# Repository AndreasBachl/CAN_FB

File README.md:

# CAN_FB_Hardware
PCB layouts for CAN field bus devices.

The layouts are stored in AUTODESK Eagle format.

Be aware that CAN does not contain any security measures.

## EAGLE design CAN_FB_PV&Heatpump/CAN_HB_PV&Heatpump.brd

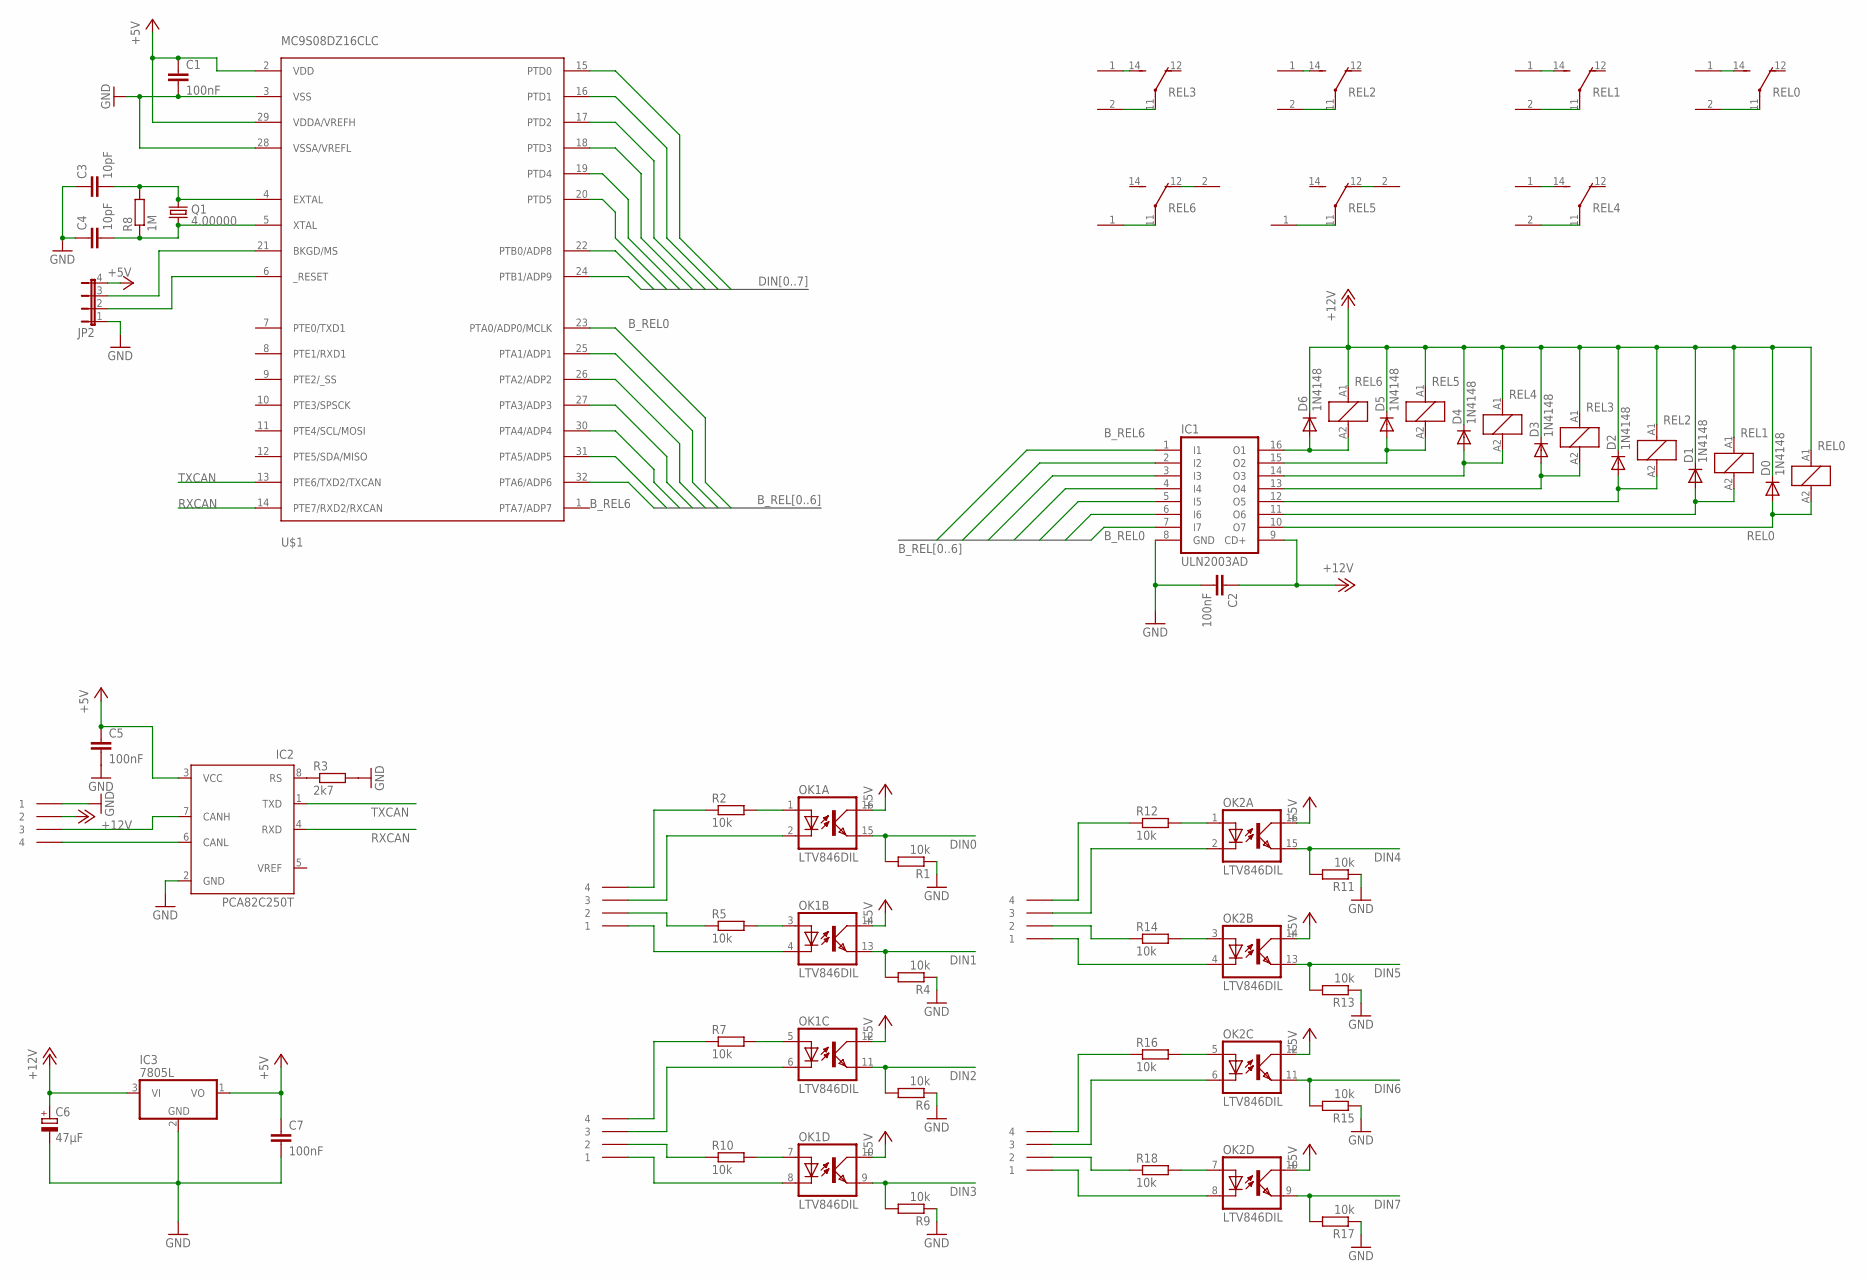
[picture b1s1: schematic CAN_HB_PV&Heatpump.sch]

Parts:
C1, C7: 100nF; C0805K
C2, C5: 100nF; C0805
C3, C4: 10pF; C0805K
C6: 47µF; E2-5
D0, D1, D2, D3, D4, D5, D6: 1N4148; SOD80C
IC1: ULN2003AD; SO16
IC2: PCA82C250T; SO8
IC3: 7805L; TO92
JP2: JP4E; JP4
KL1, KL2, KL3, KL4, KL5: AST021-04
OK1, OK2: LTV846DIL; DIL16
Q1: 4.00000; HC49U-V
R1, R2, R4, R5, R6, R7, R9, R10, R11, R12, R13, R14, R15, R16, R17, R18: 10k; R0805
R3: 2k7; R0805
R8: 1M; R0805
REL0, REL1, REL2, REL3, REL4, REL5, REL6: FIN34.51FIN34.51.7; FIN34
U$1: MC9S08DZ16CLC; LQFP32
U$2, U$3, U$4, U$5, U$6, U$14, U$15: AKL320-02

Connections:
+5V: C1.1, C5.1, C7.1, IC2.3 (VCC), IC3.1 (VO), JP2.4, OK1.10 (COL), OK1.12 (COL), OK1.14 (COL), OK1.16 (COL), OK2.10 (COL), OK2.12 (COL), OK2.14 (COL), OK2.16 (COL), U$1.2 (VDD), U$1.29 (VDDA/VREFH)
+12V: C2.1, C6.+, D0.C, D1.C, D2.C, D3.C, D4.C, D5.C, D6.C, IC1.9 (CD+), IC3.3 (VI), KL1.P$2 (2), REL0.A1 (1), REL1.A1 (1), REL2.A1 (1), REL3.A1 (1), REL4.A1 (1), REL5.A1 (1), REL6.A1 (1)
BKGD: JP2.3, U$1.21 (BKGD/MS)
B_REL0: IC1.7 (I7), U$1.23 (PTA0/ADP0/MCLK)
B_REL1: IC1.6 (I6), U$1.25 (PTA1/ADP1)
B_REL2: IC1.5 (I5), U$1.26 (PTA2/ADP2)
B_REL3: IC1.4 (I4), U$1.27 (PTA3/ADP3)
B_REL4: IC1.3 (I3), U$1.30 (PTA4/ADP4)
B_REL5: IC1.2 (I2), U$1.31 (PTA5/ADP5)
B_REL6: IC1.1 (I1), U$1.32 (PTA6/ADP6)
CANH: IC2.7 (CANH), KL1.P$3 (3)
CANL: IC2.6 (CANL), KL1.P$4 (4)
CH4: REL5.12 (O), U$5.2
DIN0: OK1.15 (EMIT), R1.2, U$1.15 (PTD0)
DIN0+: KL2.P$4 (4), R2.1
DIN0-: KL2.P$3 (3), OK1.2 (C)
DIN1: OK1.13 (EMIT), R4.2, U$1.16 (PTD1)
DIN1+: KL2.P$2 (2), R5.1
DIN1-: KL2.P$1 (1), OK1.4 (C)
DIN2: OK1.11 (EMIT), R6.2, U$1.17 (PTD2)
DIN2+: KL3.P$4 (4), R7.1
DIN2-: KL3.P$3 (3), OK1.6 (C)
DIN3: OK1.9 (EMIT), R9.2, U$1.18 (PTD3)
DIN3+: KL3.P$2 (2), R10.1
DIN3-: KL3.P$1 (1), OK1.8 (C)
DIN4: OK2.15 (EMIT), R11.2, U$1.19 (PTD4)
DIN4+: KL4.P$4 (4), R12.1
DIN4-: KL4.P$3 (3), OK2.2 (C)
DIN5: OK2.13 (EMIT), R13.2, U$1.20 (PTD5)
DIN5+: KL4.P$2 (2), R14.1
DIN5-: KL4.P$1 (1), OK2.4 (C)
DIN6: OK2.11 (EMIT), R15.2, U$1.22 (PTB0/ADP8)
DIN6+: KL5.P$4 (4), R16.1
DIN6-: KL5.P$3 (3), OK2.6 (C)
DIN7: OK2.9 (EMIT), R17.2, U$1.24 (PTB1/ADP9)
DIN7+: KL5.P$2 (2), R18.1
DIN7-: KL5.P$1 (1), OK2.8 (C)
GND: C1.2, C2.2, C3.1, C4.1, C5.2, C6.-, C7.2, IC1.8 (GND), IC2.2 (GND), IC3.2 (GND), JP2.1, KL1.P$1 (1), R1.1, R3.2, R4.1, R6.1, R9.1, R11.1, R13.1, R15.1, R17.1, U$1.3 (VSS), U$1.28 (VSSA/VREFL)
unnamed: REL3.11, U$2.2
unnamed: OK1.1 (A), R2.2
unnamed: IC2.8 (RS), R3.1
unnamed: REL6.11, U$3.1
unnamed: REL3.14 (S), U$2.1
unnamed: REL2.14 (S), U$4.1
unnamed: REL2.11, U$4.2
unnamed: C4.2, Q1.1, R8.1, U$1.5 (XTAL)
unnamed: C3.2, Q1.2, R8.2, U$1.4 (EXTAL)
unnamed: REL4.11, U$14.2
unnamed: REL4.14 (S), U$14.1
unnamed: REL1.11, U$6.2
unnamed: REL1.14 (S), U$6.1
unnamed: REL0.11, U$15.2
unnamed: REL0.14 (S), U$15.1
unnamed: REL5.11, U$5.1
unnamed: REL6.12 (O), U$3.2
unnamed: OK1.3 (A), R5.2
unnamed: OK1.5 (A), R7.2
unnamed: OK1.7 (A), R10.2
unnamed: OK2.1 (A), R12.2
unnamed: OK2.3 (A), R14.2
unnamed: OK2.5 (A), R16.2
unnamed: OK2.7 (A), R18.2
REL0: D0.A, IC1.10 (O7), REL0.A2 (2)
REL1: D1.A, IC1.11 (O6), REL1.A2 (2)
REL2: D2.A, IC1.12 (O5), REL2.A2 (2)
REL3: D3.A, IC1.13 (O4), REL3.A2 (2)
REL4: D4.A, IC1.14 (O3), REL4.A2 (2)
REL5: D5.A, IC1.15 (O2), REL5.A2 (2)
REL6: D6.A, IC1.16 (O1), REL6.A2 (2)
RESET: JP2.2, U$1.6 (_RESET)
RXCAN: IC2.4 (RXD), U$1.14 (PTE7/RXD2/RXCAN)
TXCAN: IC2.1 (TXD), U$1.13 (PTE6/TXD2/TXCAN)

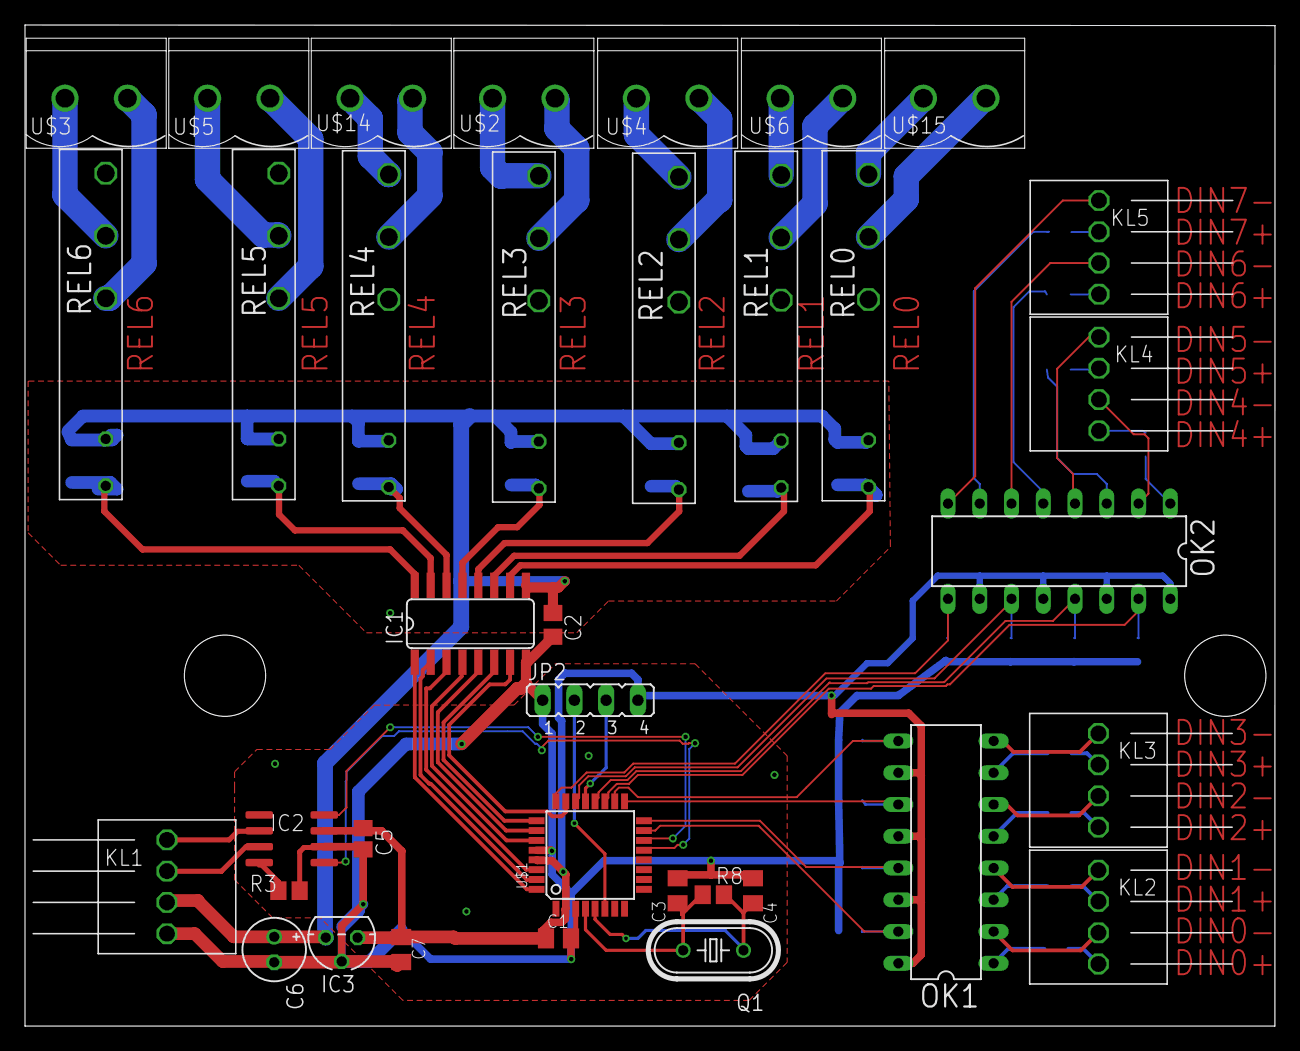
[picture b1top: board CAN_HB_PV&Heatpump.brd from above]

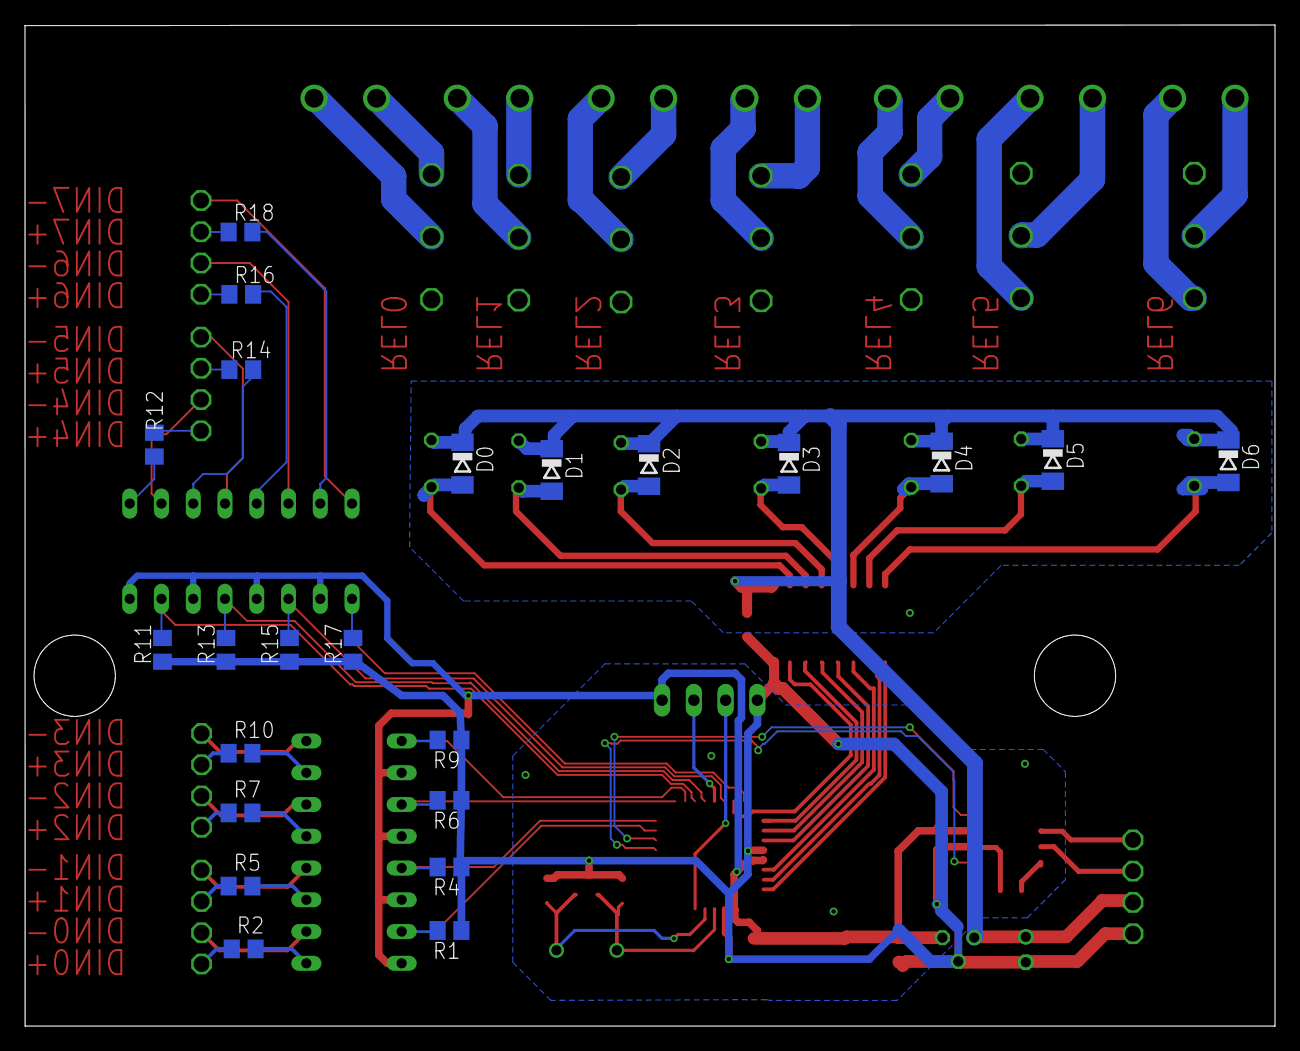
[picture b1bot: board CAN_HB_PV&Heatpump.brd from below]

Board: 2 copper layers, 100.0 x 80.1 mm, 59 parts (23 on the bottom side), 72 nets.

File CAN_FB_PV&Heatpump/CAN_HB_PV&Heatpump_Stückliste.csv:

"Qty";"Value";"Device";"Package";"Parts";"Description";"";
"1";"";"JP4E";"JP4";"JP2";"JUMPER";"";
"6";"";"R-EU_R0805";"R0805";"R7, R10, R12, R14, R16, R18";"RESISTOR, European symbol";"";
"2";"100nF";"C-EUC0805";"C0805";"C2, C5";"CAPACITOR, European symbol";"";
"2";"100nF";"C-EUC0805K";"C0805K";"C1, C7";"CAPACITOR, European symbol";"";
"10";"10k";"R-EU_R0805";"R0805";"R1, R2, R4, R5, R6, R9, R11, R13, R15, R17";"RESISTOR, European symbol";"";
"2";"10pF";"C-EUC0805K";"C0805K";"C3, C4";"CAPACITOR, European symbol";"";
"1";"1M";"R-EU_R0805";"R0805";"R8";"RESISTOR, European symbol";"";
"7";"1N4148";"DIODE-SOD80C";"SOD80C";"D0, D1, D2, D3, D4, D5, D6";"DIODE";"";
"1";"2k7";"R-EU_R0805";"R0805";"R3";"RESISTOR, European symbol";"";
"1";"4.00000";"CRYTALHC49U-V";"HC49U-V";"Q1";"CRYSTAL";"";
"1";"47µF";"CPOL-EUE2-5";"E2-5";"C6";"POLARIZED CAPACITOR, European symbol";"";
"1";"7805L";"7805L";"TO92";"IC3";"Positive VOLTAGE REGULATOR";"";
"7";"AKL320-02";"AKL320-02";"AKL320-02";"U$2, U$3, U$4, U$5, U$6, U$14, U$15";"";"";
"5";"AST021-04";"AST021-04";"AST021-04";"KL1, KL2, KL3, KL4, KL5";"";"";
"7";"FIN34.51FIN34.51.7";"FIN34.51FIN34.51.7";"FIN34";"REL0, REL1, REL2, REL3, REL4, REL5, REL6";"Finder 34.51.7 Relais";"";
"2";"LTV846DIL";"LTV846DIL";"DIL16";"OK1, OK2";"OPTO COUPLER";"";
"1";"MC9S08DZ16CLC";"MC9S08DZ16CLC";"LQFP32";"U$1";"";"";
"1";"PCA82C250T";"PCA82C250T";"SO8";"IC2";"CAN CONTROLLER INTERFACE";"";
"1";"ULN2003AD";"ULN2003AD";"SO16";"IC1";"DRIVER ARRAY";"";

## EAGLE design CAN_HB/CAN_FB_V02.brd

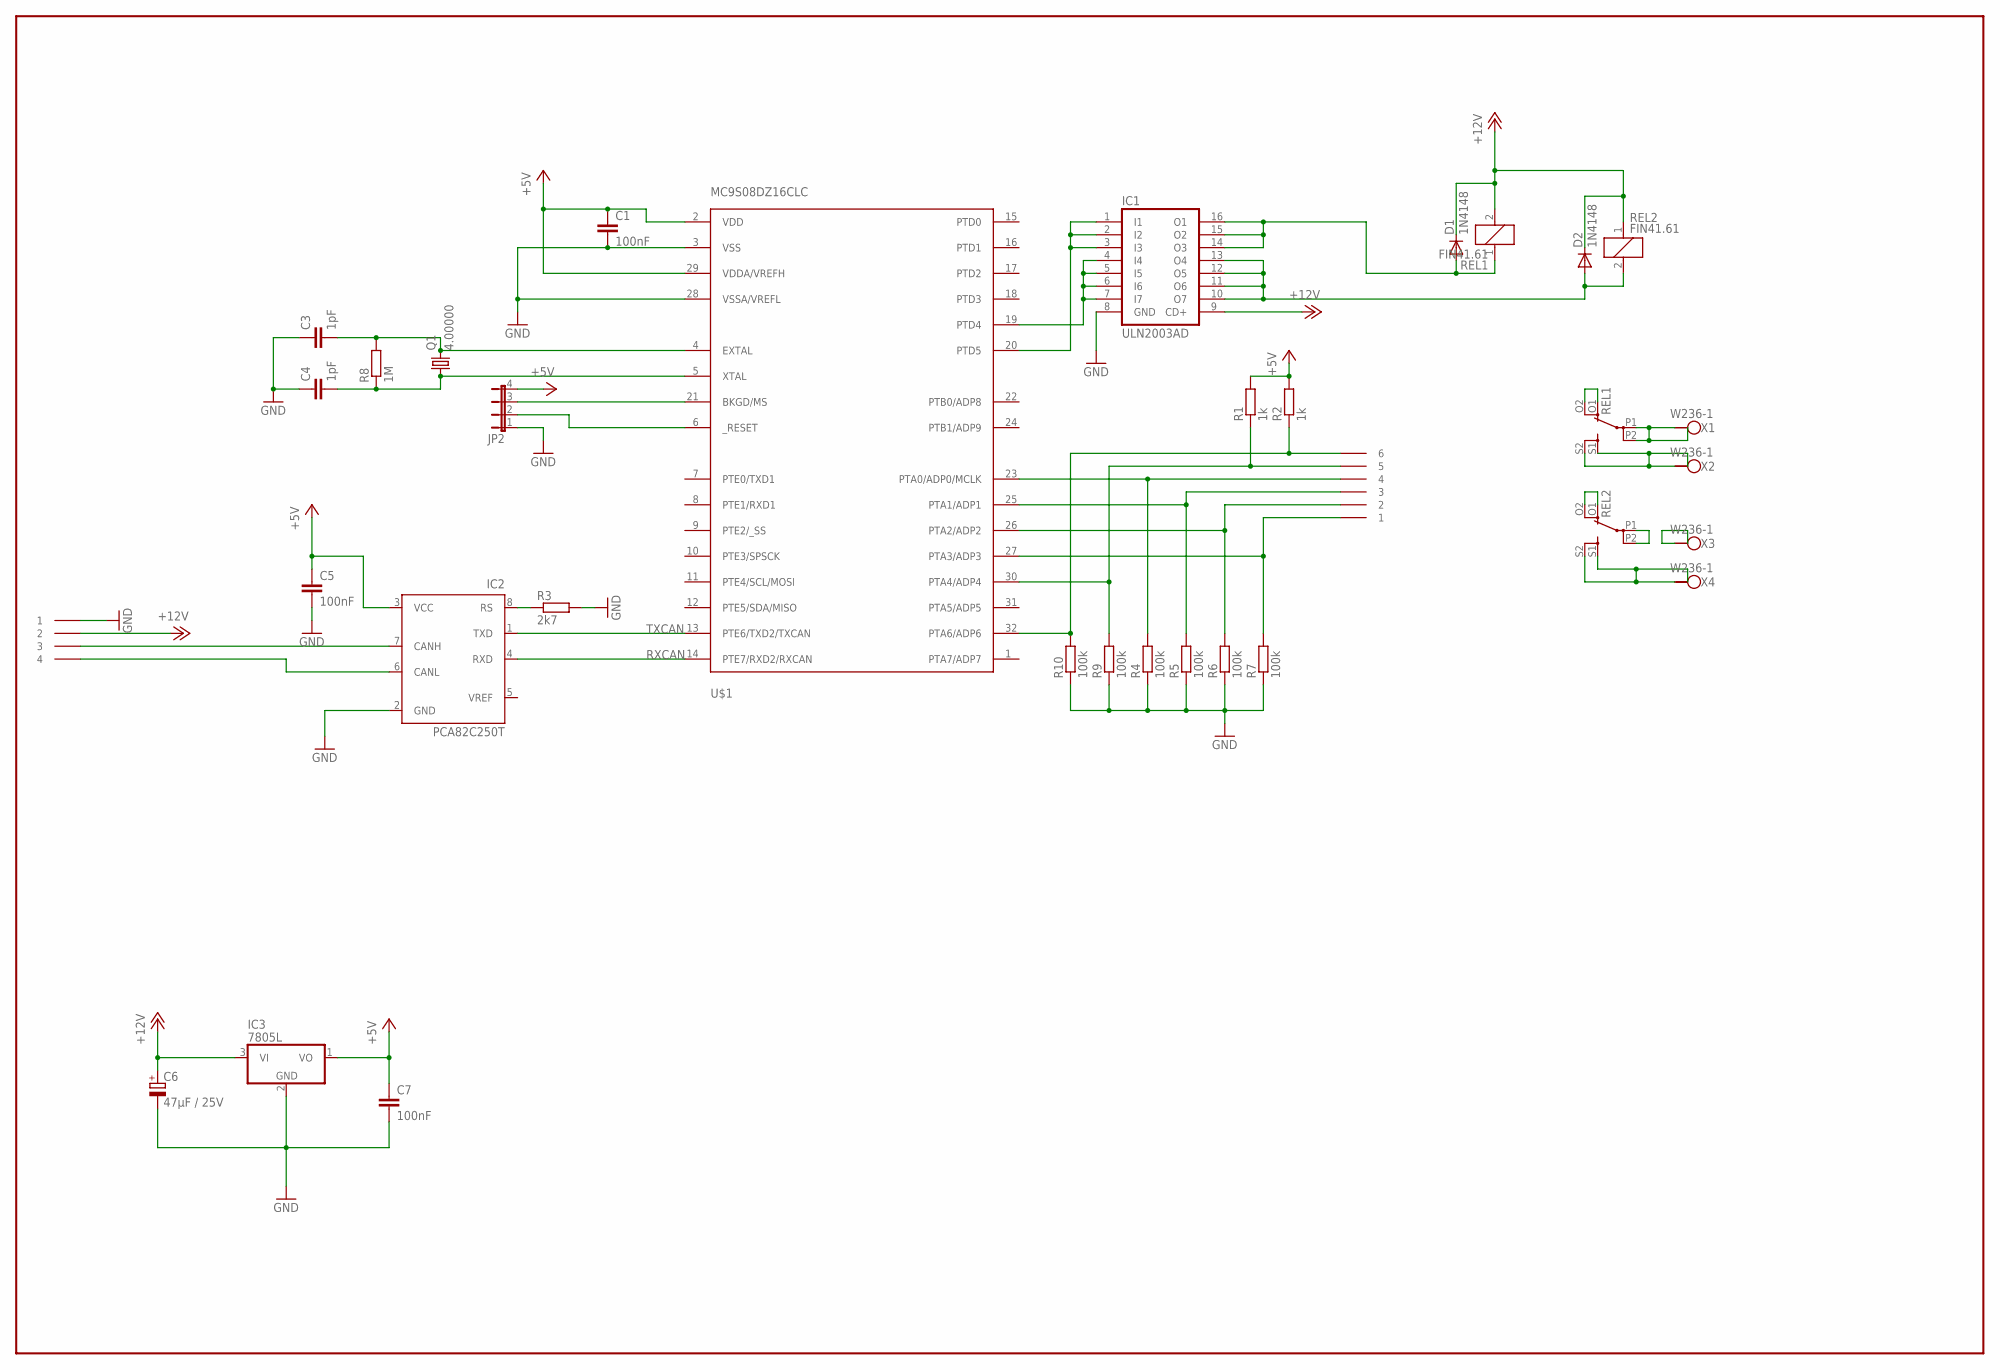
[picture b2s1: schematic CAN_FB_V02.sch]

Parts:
C1, C7: 100nF; C0805K
C3, C4: 1pF; C0805K
C5: 100nF; C0805
C6: 47µF / 25V; E2-5
D1, D2: 1N4148; SOD80C
IC1: ULN2003AD; SO16
IC2: PCA82C250T; SO8
IC3: 7805L; TO92
JP2: JP4E; JP4
KL1: AST021-04
KL2: AST021-06
Q1: 4.00000; HC49U-V
R1, R2: 1k; R0805
R3: 2k7; R0805
R4, R5, R6, R7, R9, R10: 100k; R0805
R8: 1M; R0805
REL1, REL2: FIN41.61; FIN41
U$1: MC9S08DZ16CLC; LQFP32
X1, X2, X3, X4: W236-1

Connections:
+5V: C1.1, C5.1, C7.1, IC2.3 (VCC), IC3.1 (VO), JP2.4, R1.2, R2.2, U$1.2 (VDD), U$1.29 (VDDA/VREFH)
+12V: C6.+, D1.C, D2.C, IC1.9 (CD+), IC3.3 (VI), KL1.P$2 (2), REL1.2, REL2.1
A0: KL2.P$4 (4), R4.2, U$1.23 (PTA0/ADP0/MCLK)
A1: KL2.P$3 (3), R5.2, U$1.25 (PTA1/ADP1)
A2: KL2.P$2 (2), R6.2, U$1.26 (PTA2/ADP2)
A3: KL2.P$1 (1), R7.2, U$1.27 (PTA3/ADP3)
A4: KL2.P$5 (5), R1.1, R9.2, U$1.30 (PTA4/ADP4)
A5: KL2.P$6 (6), R2.1, R10.2, U$1.32 (PTA6/ADP6)
GND: C1.2, C3.1, C4.1, C5.2, C6.-, C7.2, IC1.8 (GND), IC2.2 (GND), IC3.2 (GND), JP2.1, KL1.P$1 (1), R3.2, R4.1, R5.1, R6.1, R7.1, R9.1, R10.1, U$1.3 (VSS), U$1.28 (VSSA/VREFL)
unnamed: IC2.8 (RS), R3.1
unnamed: IC2.6 (CANL), KL1.P$4 (4)
unnamed: D1.A, IC1.14 (O3), IC1.15 (O2), IC1.16 (O1), REL1.1
unnamed: IC2.7 (CANH), KL1.P$3 (3)
unnamed: D2.A, IC1.10 (O7), IC1.11 (O6), IC1.12 (O5), IC1.13 (O4), REL2.2
unnamed: C4.2, Q1.1, R8.1, U$1.5 (XTAL)
unnamed: C3.2, Q1.2, R8.2, U$1.4 (EXTAL)
unnamed: IC1.1 (I1), IC1.2 (I2), IC1.3 (I3), U$1.20 (PTD5)
unnamed: IC1.4 (I4), IC1.5 (I5), IC1.6 (I6), IC1.7 (I7), U$1.19 (PTD4)
unnamed: REL1.S1 (S), REL1.S2 (S), X2.1 (KL1), X2.2 (KL2)
unnamed: REL1.P1, REL1.P2, X1.1 (KL1), X1.2 (KL2)
unnamed: REL1.O1 (O), REL1.O2 (O)
unnamed: JP2.2, U$1.6 (_RESET)
unnamed: JP2.3, U$1.21 (BKGD/MS)
unnamed: REL2.O1 (O), REL2.O2 (O)
unnamed: X3.1 (KL1), X3.2 (KL2)
unnamed: REL2.S1 (S), REL2.S2 (S), X4.1 (KL1), X4.2 (KL2)
unnamed: REL2.P1, REL2.P2
RXCAN: IC2.4 (RXD), U$1.14 (PTE7/RXD2/RXCAN)
TXCAN: IC2.1 (TXD), U$1.13 (PTE6/TXD2/TXCAN)

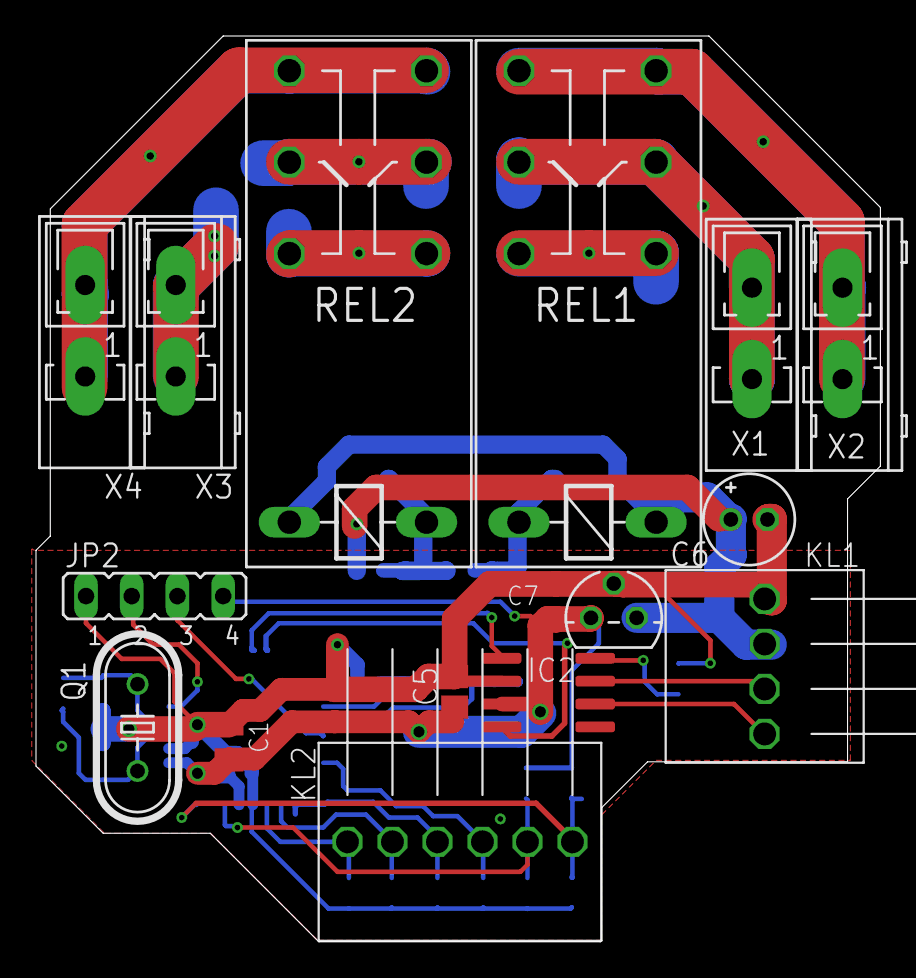
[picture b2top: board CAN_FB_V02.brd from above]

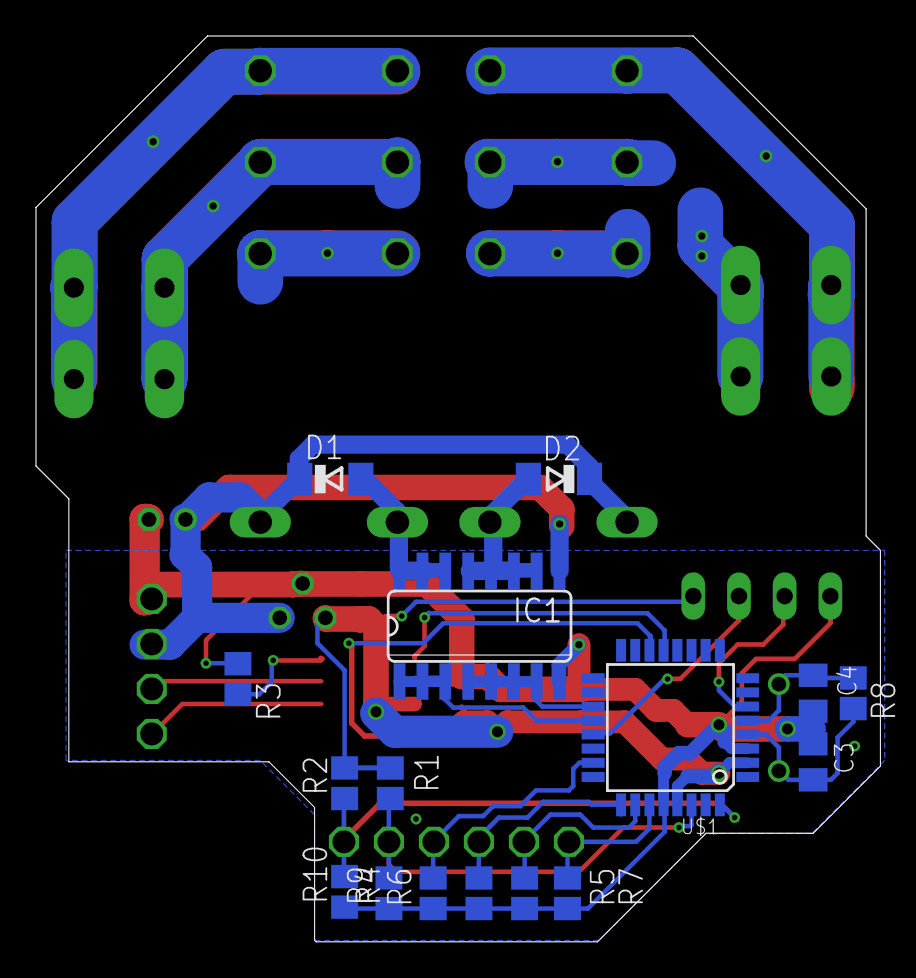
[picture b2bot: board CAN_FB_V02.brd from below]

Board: 2 copper layers, 46.9 x 50.3 mm, 32 parts (16 on the bottom side), 29 nets.

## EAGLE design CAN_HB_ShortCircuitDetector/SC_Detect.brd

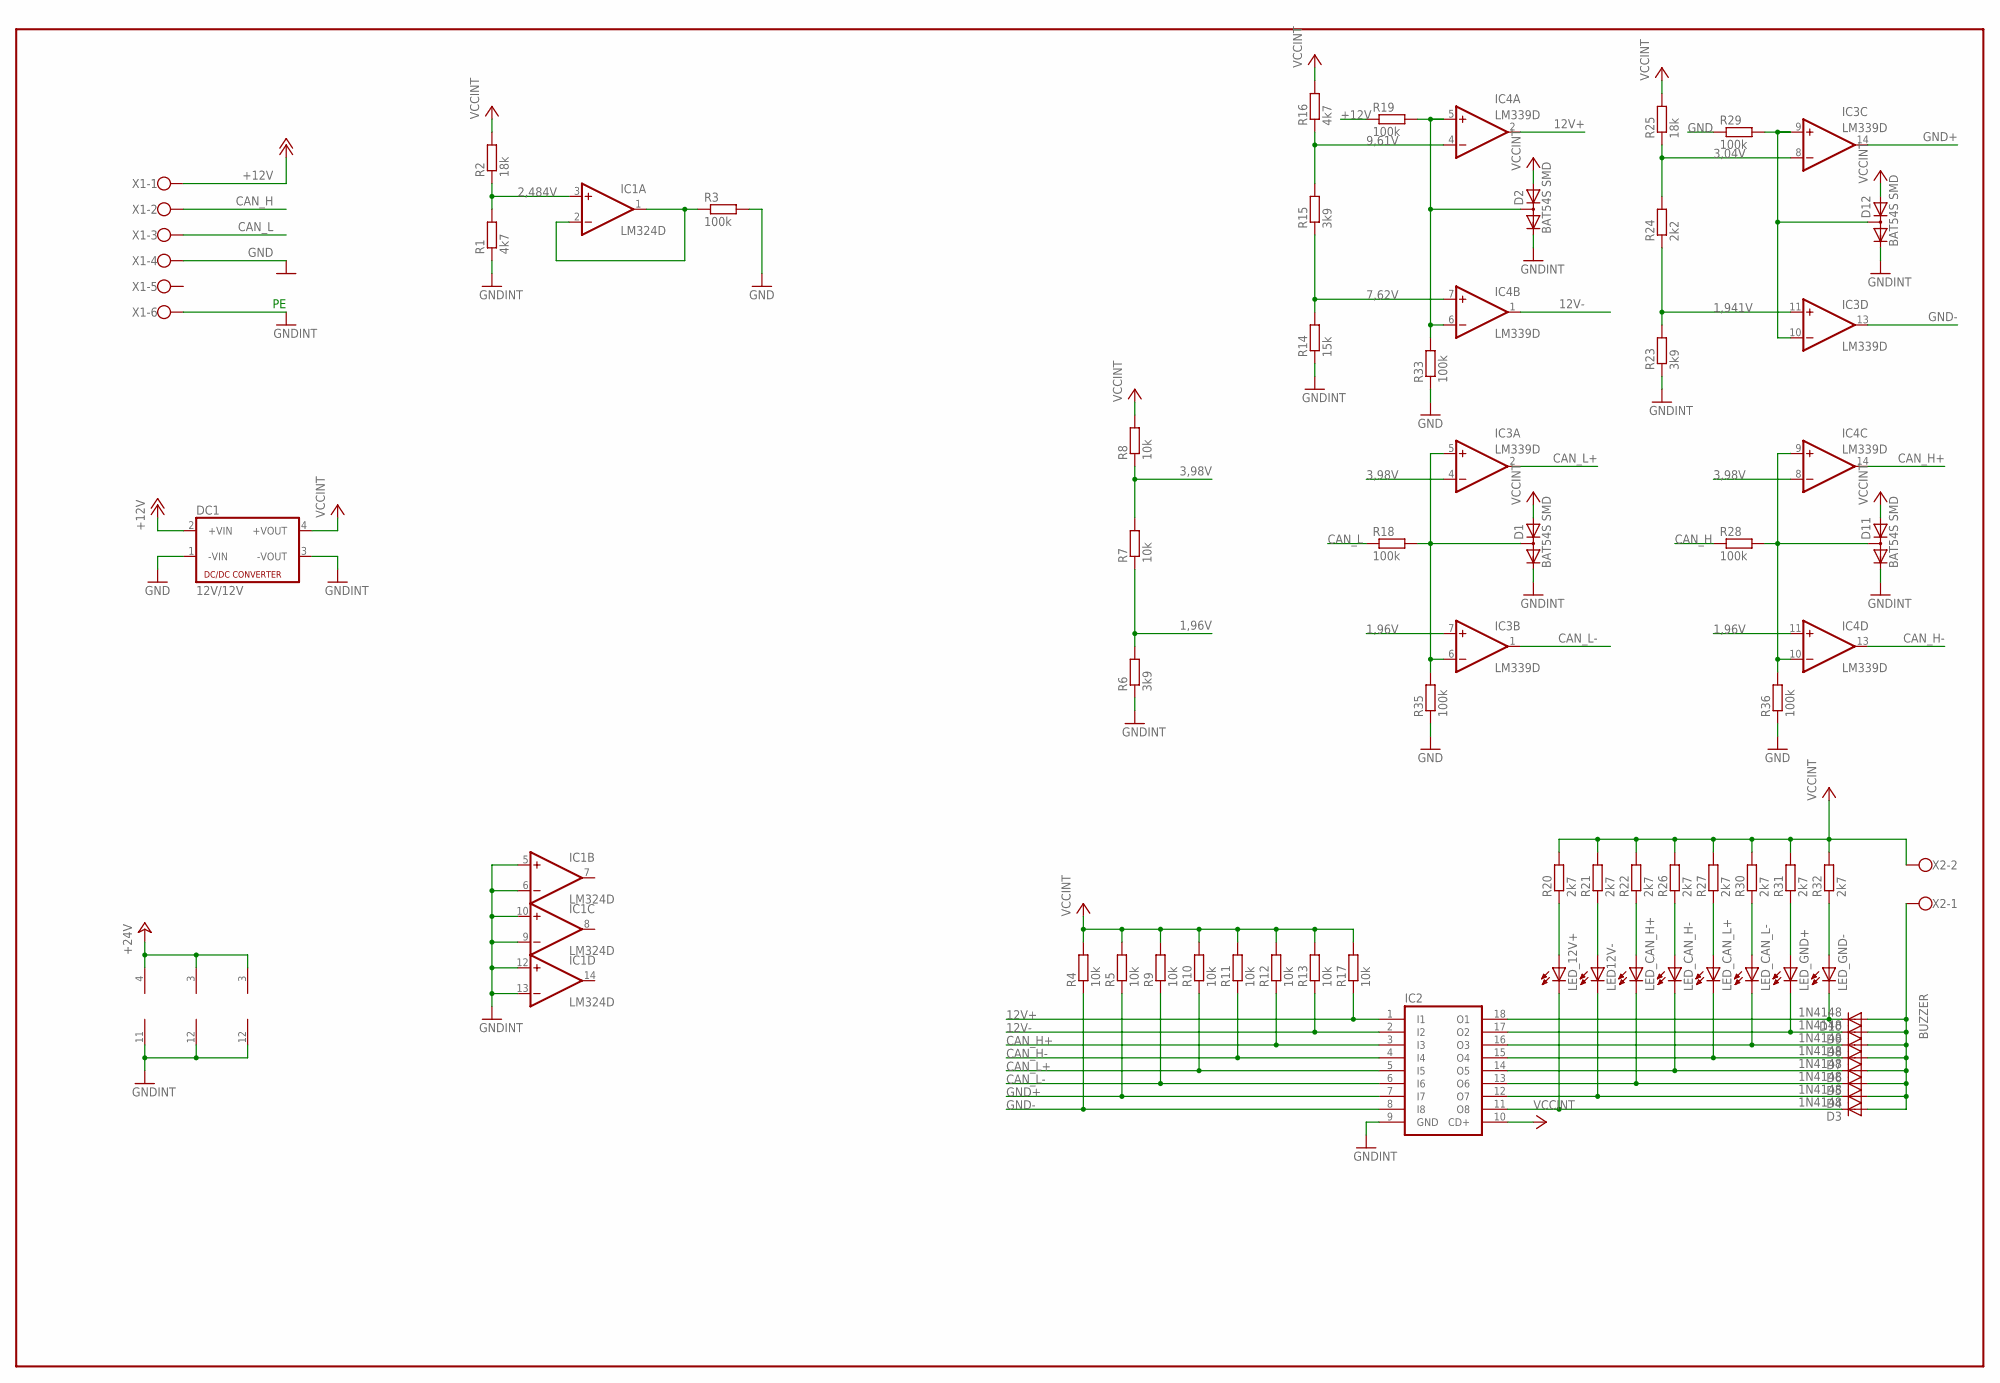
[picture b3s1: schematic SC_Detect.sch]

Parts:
D1, D2, D11, D12: BAT54S SMD; SOT23
D3, D4, D5, D6, D7, D8, D9, D10: 1N4148; SOD80C
DC1: 12V/12V; NME
IC1: LM324D; SO14
IC2: ULN2803AD; SO18L
IC3, IC4: LM339D; SO14
LED12V-: LED_3MM_ST_RT; LED3MM
LED_12V+: LED_3MM_ST_RT; LED3MM
LED_CAN_H+: LED_3MM_ST_RT; LED3MM
LED_CAN_H-: LED_3MM_ST_RT; LED3MM
LED_CAN_L+: LED_3MM_ST_RT; LED3MM
LED_CAN_L-: LED_3MM_ST_RT; LED3MM
LED_GND+: LED_3MM_ST_RT; LED3MM
LED_GND-: LED_3MM_ST_RT; LED3MM
R1, R16: 4k7; R0805
R2, R25: 18k; R0805
R3, R18, R19, R28, R29, R33, R35, R36: 100k; R0805
R4, R5, R7, R8, R9, R10, R11, R12, R13, R17: 10k; R0805
R6, R15, R23: 3k9; R0805
R14: 15k; R0805
R20, R21, R22, R26, R27, R30, R31, R32: 2k7; R0805
R24: 2k2; R0805
X1: W237-136
X2: W237-102

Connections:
1,96V: IC3.7 (+IN), IC4.11 (+IN), R6.2, R7.1
1,941V: IC3.11 (+IN), R23.2, R24.1
2,484V: IC1.3 (+IN), R1.2, R2.1
3,04V: IC3.8 (-IN), R24.2, R25.1
3,98V: IC3.4 (-IN), IC4.8 (-IN), R7.2, R8.1
7,62V: IC4.7 (+IN), R14.2, R15.1
9,61V: IC4.4 (-IN), R15.2, R16.1
12V+: IC2.1 (I1), IC4.2 (OUT), R17.1
12V+1: D10.C, IC2.18 (O1), LED_GND-.K (C)
12V-: IC2.2 (I2), IC4.1 (OUT), R13.1
+12V: DC1.2 (+VIN), R19.1, X1.1
BUZZER: D3.A, D4.A, D5.A, D6.A, D7.A, D8.A, D9.A, D10.A, X2.1
CAN_H: R28.1, X1.2
CAN_H+: IC2.3 (I3), IC4.14 (OUT), R12.1
CAN_H-: IC2.4 (I4), IC4.13 (OUT), R11.1
CAN_L: R18.1, X1.3
CAN_L+: IC2.5 (I5), IC3.2 (OUT), R10.1
CAN_L-: IC2.6 (I6), IC3.1 (OUT), R9.1
GND: DC1.1 (-VIN), R3.2, R29.1, R33.1, R35.1, R36.1, X1.4
GND+: IC2.7 (I7), IC3.14 (OUT), R5.1
GND-: IC2.8 (I8), IC3.13 (OUT), R4.1
GNDINT: D1.2 (C), D2.2 (C), D11.2 (C), D12.2 (C), DC1.3 (-VOUT), IC1.5 (+IN), IC1.6 (-IN), IC1.9 (-IN), IC1.10 (+IN), IC1.11 (V-), IC1.12 (+IN), IC1.13 (-IN), IC2.9 (GND), IC3.12 (V-), IC4.12 (V-), R1.1, R6.1, R14.1, R23.1, X1.6
unnamed: IC1.1 (OUT), IC1.2 (-IN), R3.1
unnamed: LED_GND-.A, R32.1
unnamed: LED_GND+.A, R31.1
unnamed: LED_CAN_L-.A, R30.1
unnamed: LED_CAN_L+.A, R27.1
unnamed: LED_CAN_H-.A, R26.1
unnamed: LED_CAN_H+.A, R22.1
unnamed: LED12V-.A, R21.1
unnamed: D12.3 (AC), IC3.9 (+IN), IC3.10 (-IN), R29.2
unnamed: D11.3 (AC), IC4.9 (+IN), IC4.10 (-IN), R28.2, R36.2
unnamed: LED_12V+.A, R20.1
unnamed: D3.C, IC2.11 (O8), LED_12V+.K (C)
unnamed: D4.C, IC2.12 (O7), LED12V-.K (C)
unnamed: D2.3 (AC), IC4.5 (+IN), IC4.6 (-IN), R19.2, R33.2
unnamed: D5.C, IC2.13 (O6), LED_CAN_H+.K (C)
unnamed: D6.C, IC2.14 (O5), LED_CAN_H-.K (C)
unnamed: D7.C, IC2.15 (O4), LED_CAN_L+.K (C)
unnamed: D8.C, IC2.16 (O3), LED_CAN_L-.K (C)
unnamed: D9.C, IC2.17 (O2), LED_GND+.K (C)
unnamed: D1.3 (AC), IC3.5 (+IN), IC3.6 (-IN), R18.2, R35.2
VCCINT: D1.1 (A), D2.1 (A), D11.1 (A), D12.1 (A), DC1.4 (+VOUT), IC1.4 (V+), IC2.10 (CD+), IC3.3 (V+), IC4.3 (V+), R2.2, R4.2, R5.2, R8.2, R9.2, R10.2, R11.2, R12.2, R13.2, R16.2, R17.2, R20.2, R21.2, R22.2, R25.2, R26.2, R27.2, R30.2, R31.2, R32.2, X2.2

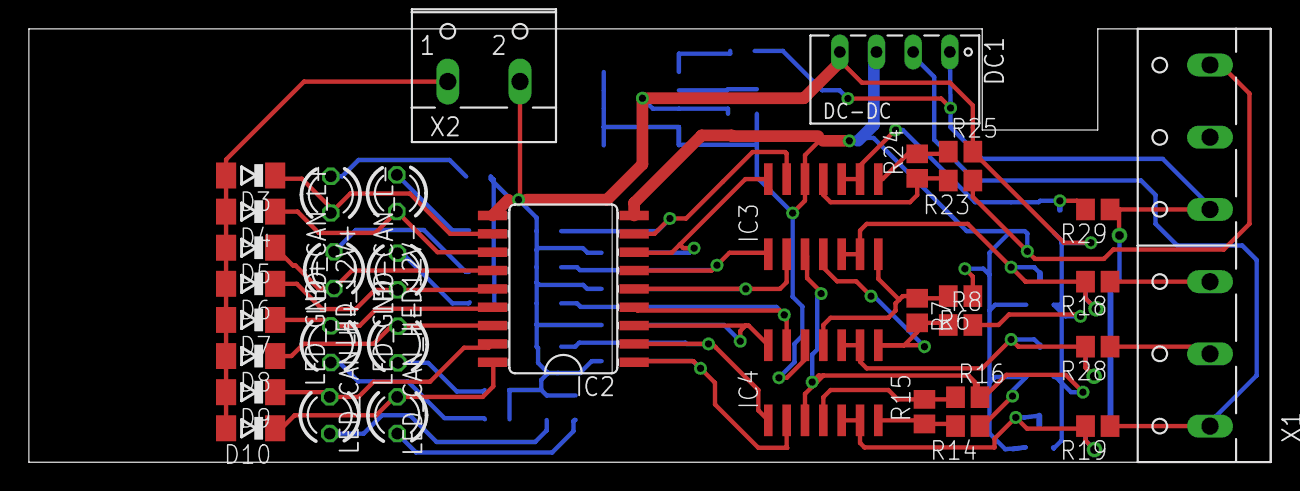
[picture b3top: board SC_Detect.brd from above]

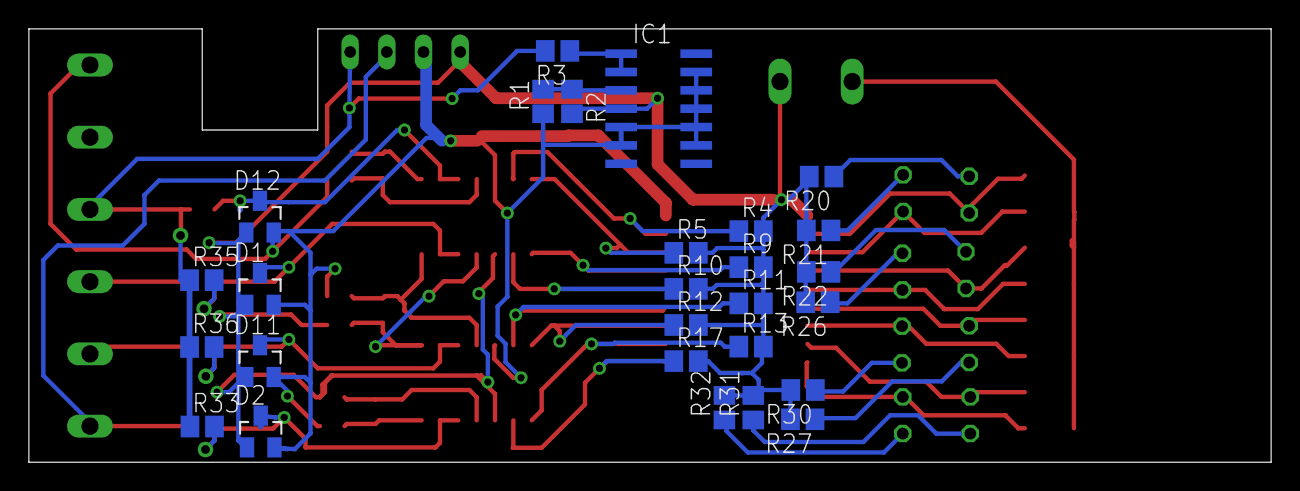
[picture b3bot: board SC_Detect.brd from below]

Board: 2 copper layers, 86.0 x 30.0 mm, 62 parts (27 on the bottom side), 43 nets.

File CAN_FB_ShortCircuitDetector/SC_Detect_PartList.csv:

"Qty";"Value";"Device";"Package";"Parts";"Description";"";
"1";"";"ULN2803AD";"SO18L";"IC2";"DRIVER ARRAY";"";
"1";"";"W237-136";"W237-136";"X1";"WAGO SCREW CLAMP";"";
"8";"100k";"R-EU_R0805";"R0805";"R3, R18, R19, R28, R29, R33, R35, R36";"RESISTOR, European symbol";"";
"10";"10k";"R-EU_R0805";"R0805";"R4, R5, R7, R8, R9, R10, R11, R12, R13, R17";"RESISTOR, European symbol";"";
"1";"12V/12V";"NME";"NME";"DC1";"DC-DC CONVERTER";"";
"1";"15k";"R-EU_R0805";"R0805";"R14";"RESISTOR, European symbol";"";
"2";"18k";"R-EU_R0805";"R0805";"R2, R25";"RESISTOR, European symbol";"";
"8";"1N4148";"DIODE-SOD80C";"SOD80C";"D3, D4, D5, D6, D7, D8, D9, D10";"DIODE";"";
"1";"2k2";"R-EU_R0805";"R0805";"R24";"RESISTOR, European symbol";"";
"8";"2k7";"R-EU_R0805";"R0805";"R20, R21, R22, R26, R27, R30, R31, R32";"RESISTOR, European symbol";"";
"3";"3k9";"R-EU_R0805";"R0805";"R6, R15, R23";"RESISTOR, European symbol";"";
"2";"4k7";"R-EU_R0805";"R0805";"R1, R16";"RESISTOR, European symbol";"";
"4";"BAT54S SMD";"DIODE_2CACA-SOT23";"SOT23";"D1, D2, D11, D12";"2 Diodes - Cathode-Anode|Cathode-Anode";"";
"1";"EB2209A";"EB2209A";"EB2209A";"SG1";"BUZZER Source: Buerklin";"";
"8";"LED_3MM_ST_RT";"LED3MM";"LED3MM";"LED12V-, LED_12V+, LED_CAN_H+, LED_CAN_H-, LED_CAN_L+, LED_CAN_L-, LED_GND+, LED_GND-";"LED";"";
"1";"LM324D";"LM324D";"SO14";"IC1";"OP AMP";"";
"2";"LM339D";"LM339D";"SO14";"IC3, IC4";"COMPARATOR";"";

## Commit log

2011-08-21 hardware added
2011-10-13 Alles aus beim Startup Rollotimer für Türen verlängert
2011-12-04 AmbTempController added
2011-12-04 AmbTempController added Project restructured
2014-10-04 Short CircuitDetection added
2017-11-04 some update
2017-11-05 CAN_HB_PV&Heatpump initial checkin
2017-11-07 hardware finalized
2018-01-29 PV_Heatpump Wiring plan added Firmware setup done
2018-02-11 PV-Heatpump_Control working
2018-05-25 manuell schaltbare EVU-Abschaltung hinzugefügt
2023-10-25 cleanup
2023-10-28 =cleanup
